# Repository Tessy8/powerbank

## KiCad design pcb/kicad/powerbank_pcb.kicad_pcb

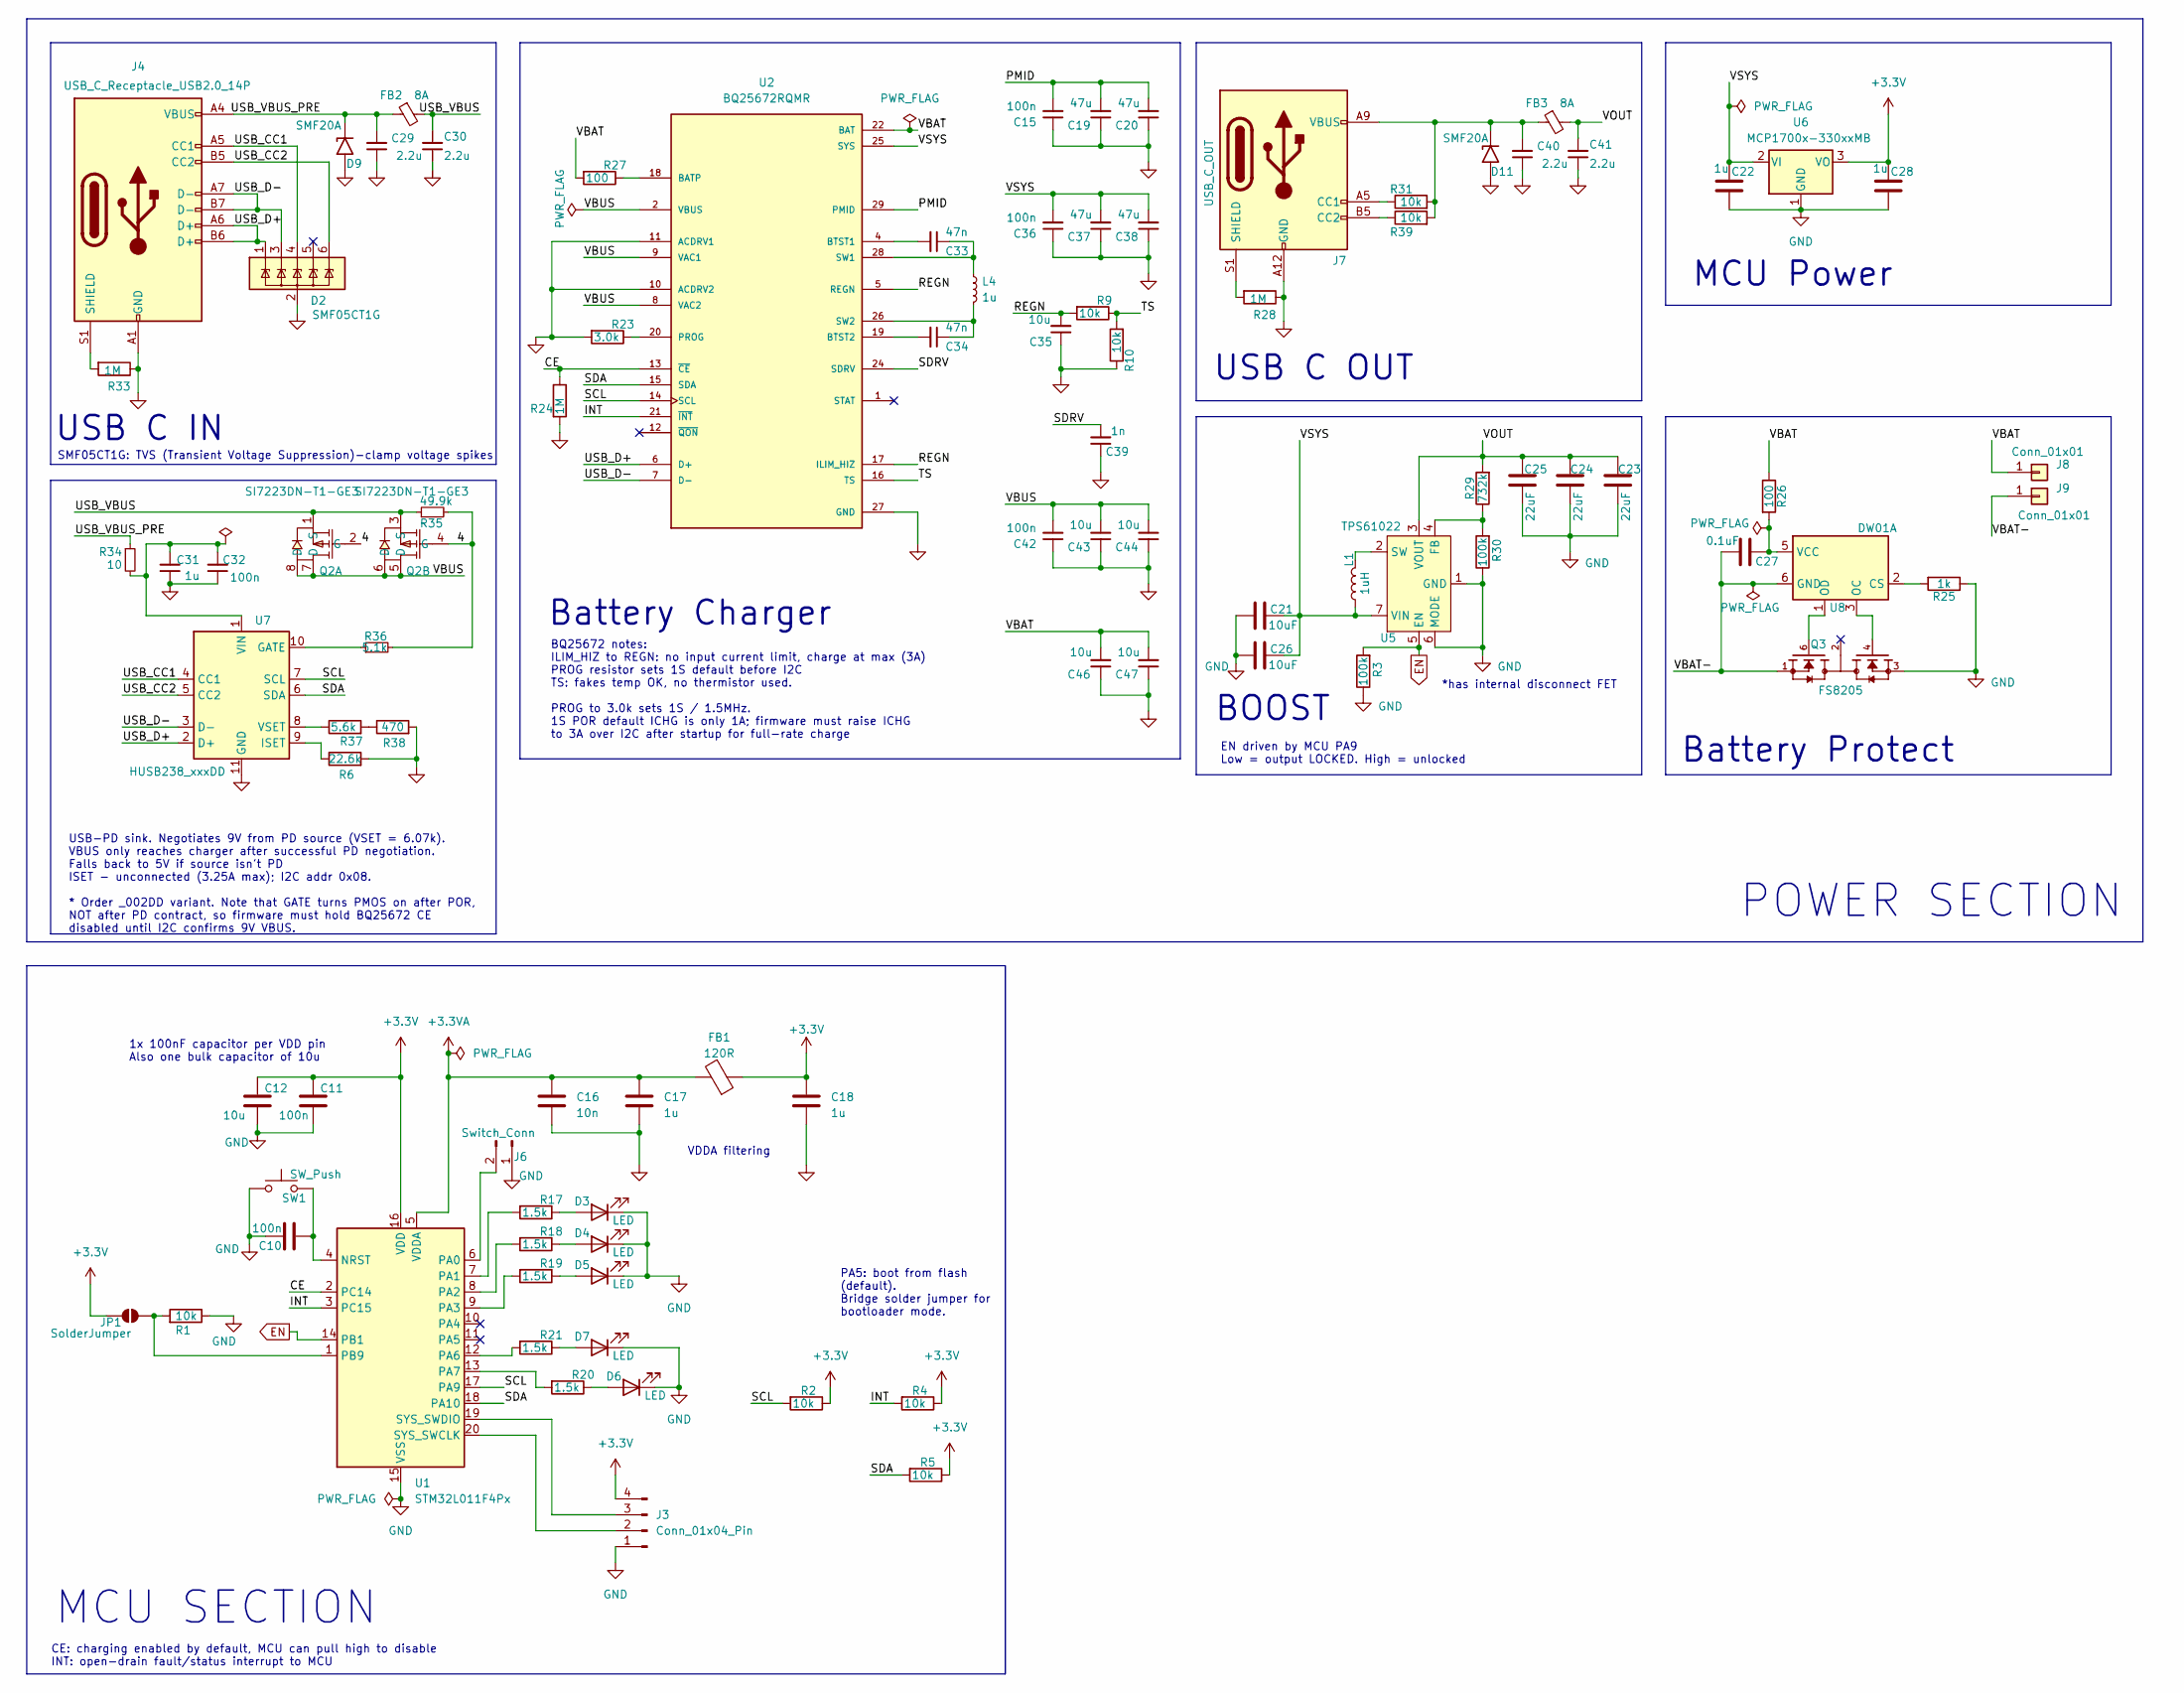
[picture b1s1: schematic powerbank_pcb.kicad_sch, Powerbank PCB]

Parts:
C10, C11, C32, C42: 100n; C_0603_1608Metric
C12, C35, C43, C44, C46, C47: 10u; C_0805_2012Metric
C15, C36: 100n; C_0805_2012Metric
C16: 10n; C_0603_1608Metric
C17, C18, C22, C28, C31: 1u; C_0603_1608Metric
C19, C20, C37, C38: 47u; C_0805_2012Metric
C21, C26: 10uF; C_0805_2012Metric
C23, C24, C25: 22uF; C_0805_2012Metric
C27: 0.1uF; C_0603_1608Metric
C29, C30, C40, C41: 2.2u; C_0603_1608Metric
C33, C34: 47n; C_0603_1608Metric
C39: 1n; C_0402_1005Metric
D2: SMF05CT1G; SOT-23-6
D3, D4, D5, D6, D7: LED; LED_0805_2012Metric
D9, D11: SMF20A; D_SMF
FB1: 120R; L_0805_2012Metric
FB2, FB3: 8A; L_0805_2012Metric
J3: Conn_01x04_Pin; PinHeader_1x04_P2.54mm_Vertical
J4: USB_C_Receptacle_USB2.0_14P; USB_C_Receptacle_GCT_USB4105-xx-A_16P_TopMnt_Horizontal
J6: Switch_Conn; PinHeader_1x02_P2.54mm_Vertical
J7: USB_C_OUT; USB_C_Receptacle_GCT_USB4125-xx-x_6P_TopMnt_Horizontal
J8, J9: Conn_01x01; TestPoint_THTPad_2.0x2.0mm_Drill1.0mm
JP1: SolderJumper; SolderJumper-2_P1.3mm_Open_RoundedPad1.0x1.5mm
L1: 1uH; L_Coilcraft_XAL7030-102
L4: 1u; L_Changjiang_FXL0530
Q2: SI7223DN-T1-GE3; PDFN3333-8_L3.1-W3.1-P0.65-LS3.4-BL-EP; MPN SI7223DN-T1-GE3; LCSC Part C17406449
Q3: FS8205; SOT95P280X145-6N; PARTREV 1.9
R1, R2, R4, R5, R31, R39: 10k; R_0603_1608Metric
R3, R30: 100k; R_0603_1608Metric
R6: 22.6k; R_0603_1608Metric
R9, R10: 10k; R_0805_2012Metric
R17, R18, R19, R20, R21: 1.5k; R_0603_1608Metric
R23: 3.0k; R_0603_1608Metric
R24, R28, R33: 1M; R_0603_1608Metric
R25: 1k; R_0603_1608Metric
R26, R27: 100; R_0603_1608Metric
R29: 732k; R_0603_1608Metric
R34: 10; R_0603_1608Metric
R35: 49.9k; R_0603_1608Metric
R36: 5.1k; R_0603_1608Metric
R37: 5.6k; R_0603_1608Metric
R38: 470; R_0603_1608Metric
SW1: SW_Push; SW_SPST_B3U-1000P
U1: STM32L011F4Px; TSSOP-20_4.4x6.5mm_P0.65mm
U2: BQ25672RQMR; IC_BQ25672RQMR; PARTREV A
U5: TPS61022; Texas_RWU0007A_VQFN-7_2x2mm_P0.5mm
U6: MCP1700x-330xxMB; SOT-89-3
U7: HUSB238_xxxDD; WDFN-10-1EP_3x3mm_P0.5mm_EP1.8x2.5mm
U8: DW01A; SOT-23-6

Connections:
+3.3V: C11.1, C12.1, C18.1, C28.1, FB1.1, J3.4, JP1.1 (A), R2.1, R4.1, R5.1, U1.16 (VDD), U6.3 (VO)
+3.3VA: C16.1, C17.1, FB1.2, U1.5 (VDDA)
/4: Q2.2 (G), Q2.4 (G), R35.2, R36.2
/CE: R24.1, U1.2 (PC14), U2.13 (~CE)
/INT: R4.2, U1.3 (PC15), U2.21 (~INT)
/PMID: C15.2, C19.2, C20.2, U2.29 (PMID)
/REGN: C35.2, R9.2, U2.5 (REGN), U2.17 (ILIM_HIZ)
/SCL: R2.2, U1.17 (PA9), U2.14 (SCL), U7.7 (SCL)
/SDA: R5.2, U1.18 (PA10), U2.15 (SDA), U7.6 (SDA)
/SDRV: C39.2, U2.24 (SDRV)
/TS: R9.1, R10.2, U2.16 (TS)
/USB_CC1: D2.4 (IO3), J4.A5 (CC1), U7.4 (CC1)
/USB_CC2: D2.6 (IO5), J4.B5 (CC2), U7.5 (CC2)
/USB_D+: D2.1 (IO1), J4.A6 (D+), J4.B6 (D+), U2.6 (D+), U7.2 (D+)
/USB_D-: D2.3 (IO2), J4.A7 (D-), J4.B7 (D-), U2.7 (D-), U7.3 (D-)
/USB_VBUS: C30.2, FB2.2, Q2.1 (S), Q2.3 (S), R35.1
/USB_VBUS_PRE: C29.2, D9.1 (A1), FB2.1, J4.A4 (VBUS), J4.A9 (VBUS), J4.B4 (VBUS), J4.B9 (VBUS), R34.1
/VBAT-: C27.2, J9.1, Q3.1, U8.6 (GND)
/VBUS: C42.2, C43.2, C44.2, Q2.5 (D), Q2.6 (D), Q2.7 (D), Q2.8 (D), U2.2 (VBUS), U2.3 (VBUS), U2.8 (VAC2), U2.9 (VAC1)
/VOUT: C23.2, C24.2, C25.2, C41.2, FB3.2, R29.2, U5.3 (VOUT)
/VSYS: C21.1, C22.1, C26.1, C36.2, C37.2, C38.2, L1.1, U2.25 (SYS), U5.7 (VIN), U6.2 (VI)
BAT: C46.2, C47.2, J8.1, R26.1, R27.2, U2.22 (BAT), U2.23 (BAT)
EN: R3.2, U1.14 (PB1), U5.5 (EN)
GND: C10.1, C11.2, C12.2, C15.1, C16.2, C17.2, C18.2, C19.1, C20.1, C21.2, C22.2, C23.1, C24.1, C25.1, C26.2, C28.2, C29.1, C30.1, C31.1, C32.1, C35.1, C36.1, C37.1, C38.1, C39.1, C40.1, C41.1, C42.1, C43.1, C44.1, C46.1, C47.1, D2.2 (GND), D3.1 (K), D4.1 (K), D5.1 (K), D6.1 (K), D7.1 (K), D9.2 (A2), D11.2 (A2), J3.1, J4.A1 (GND), J4.A12 (GND), J4.B1 (GND), J4.B12 (GND), J6.1, J7.A12 (GND), J7.B12 (GND), Q3.3, R1.1, R3.1, R6.2, R10.1, R23.2, R24.2, R25.1, R28.1, R30.1, R33.1, R38.2, SW1.1, U1.15 (VSS), U2.10 (ACDRV2), U2.11 (ACDRV1), U2.27 (GND), U5.1 (GND), U5.6 (MODE), U6.1 (GND), U7.11 (GND)
unnamed: D3.2 (A), R17.1
unnamed: D4.2 (A), R18.1
unnamed: D5.2 (A), R19.1
unnamed: D6.2 (A), R20.1
unnamed: D7.2 (A), R21.1
unnamed: C40.2, D11.1 (A1), FB3.1, J7.A9 (VBUS), J7.B9 (VBUS), R31.2, R39.2
unnamed: J3.2, U1.20 (SYS_SWCLK)
unnamed: J3.3, U1.19 (SYS_SWDIO)
unnamed: J4.S1 (SHIELD), R33.2
unnamed: J6.2, U1.6 (PA0)
unnamed: J7.A5 (CC1), R31.1
unnamed: J7.B5 (CC2), R39.1
unnamed: J7.S1 (SHIELD), R28.2
unnamed: JP1.2 (B), R1.2, U1.1 (PB9)
unnamed: R37.2, R38.1
unnamed: C10.2, SW1.2, U1.4 (NRST)
unnamed: R17.2, U1.7 (PA1)
unnamed: R18.2, U1.8 (PA2)
unnamed: R19.2, U1.9 (PA3)
unnamed: R21.2, U1.12 (PA6)
unnamed: R20.2, U1.13 (PA7)
unnamed: R27.1, U2.18 (BATP)
unnamed: C33.2, U2.4 (BTST1)
unnamed: C34.2, U2.19 (BTST2)
unnamed: R23.1, U2.20 (PROG)
unnamed: C33.1, L4.1, U2.28 (SW1)
unnamed: C34.1, L4.2, U2.26 (SW2)
unnamed: R29.1, R30.2, U5.4 (FB)
unnamed: L1.2, U5.2 (SW)
unnamed: R36.1, U7.10 (GATE)
unnamed: R6.1, U7.9 (ISET)
unnamed: C31.2, C32.2, R34.2, U7.1 (VIN)
unnamed: R37.1, U7.8 (VSET)
unnamed: R25.2, U8.2 (CS)
unnamed: Q3.4, U8.3 (OC)
unnamed: Q3.6, U8.1 (OD)
unnamed: C27.1, R26.2, U8.5 (VCC)

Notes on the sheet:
MCU SECTION
BQ25672 notes: ILIM_HIZ to REGN: no input current limit, charge at max (3A) PROG resistor sets 1S default before I2C TS: fakes temp OK, no thermistor used. PROG to 3.0k sets 1S / 1.5MHz. 1S POR default ICHG is only 1A; firmware must raise ICHG to 3A over I2C after startup for full-rate charge
POWER SECTION
CE: charging enabled by default, MCU can pull high to disable INT: open-drain fault/status interrupt to MCU
Battery Protect
BOOST
USB C OUT
EN driven by MCU PA9 Low = output LOCKED. High = unlocked
VDDA filtering
SMF05CT1G: TVS (Transient Voltage Suppression)-clamp voltage spikes
PA5: boot from flash (default). Bridge solder jumper for bootloader mode.
USB C IN
MCU Power
*has internal disconnect FET
1x 100nF capacitor per VDD pin Also one bulk capacitor of 10u
USB-PD sink. Negotiates 9V from PD source (VSET = 6.07k). VBUS only reaches charger after successful PD negotiation. Falls back to 5V if source isn't PD ISET - unconnected (3.25A max); I2C addr 0x08. * Order _002DD variant. Note that GATE turns PMOS on after POR, NOT after PD contract, so firmware 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
Battery Charger

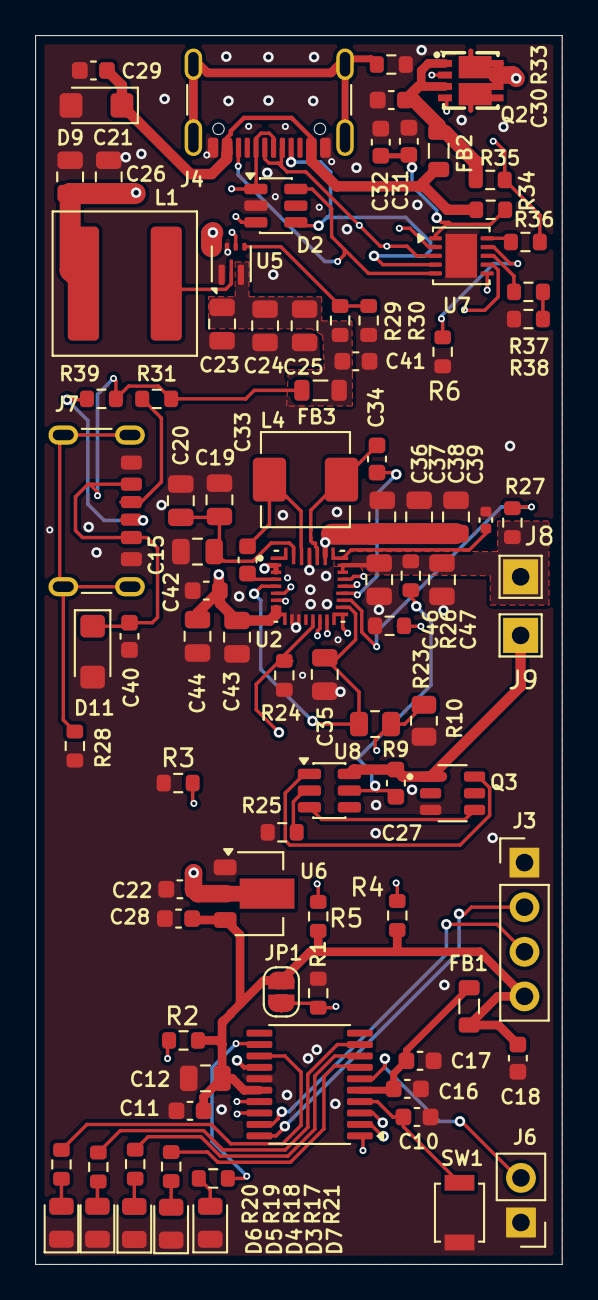
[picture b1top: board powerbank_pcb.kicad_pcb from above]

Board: 4 copper layers, 30.0 x 70.0 mm, 93 parts (0 on the bottom side), 61 nets.
